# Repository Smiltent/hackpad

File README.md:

# Smil's Hackpad
a Mini-keyboard (Marcopad) provided by Hackclub's Blueprint YSWS
# Features
* mmm... funny macro buttons!
* mmm... two funny little leds that may or may not work
# Images
## PCB & Schematic
If you look at the previous commit, you can see how much I hated my v1 PCB design. I don't even want to share it...  

## CAD model
(insert image here)
# Challenges
Getting Fusion360 on Linux...  
I tried every method, trying my hardest to NOT go on Windows, but at the end, I gave up and went on Windows...
# End Result
I feel like later on, I will try and design a better case for it, as the current one is made help with the guide.  
This has actually inspired me to try and make something else down the line.  
# BOM
* 1x SEEEDUINO XIAO RP2040
* 8x Cherry MX Switches
* 2x SK6812 MINI Leds
* 4x Blank DSA Keycaps
* 4x M3x16 Bolt
* 4x M3 Heatset

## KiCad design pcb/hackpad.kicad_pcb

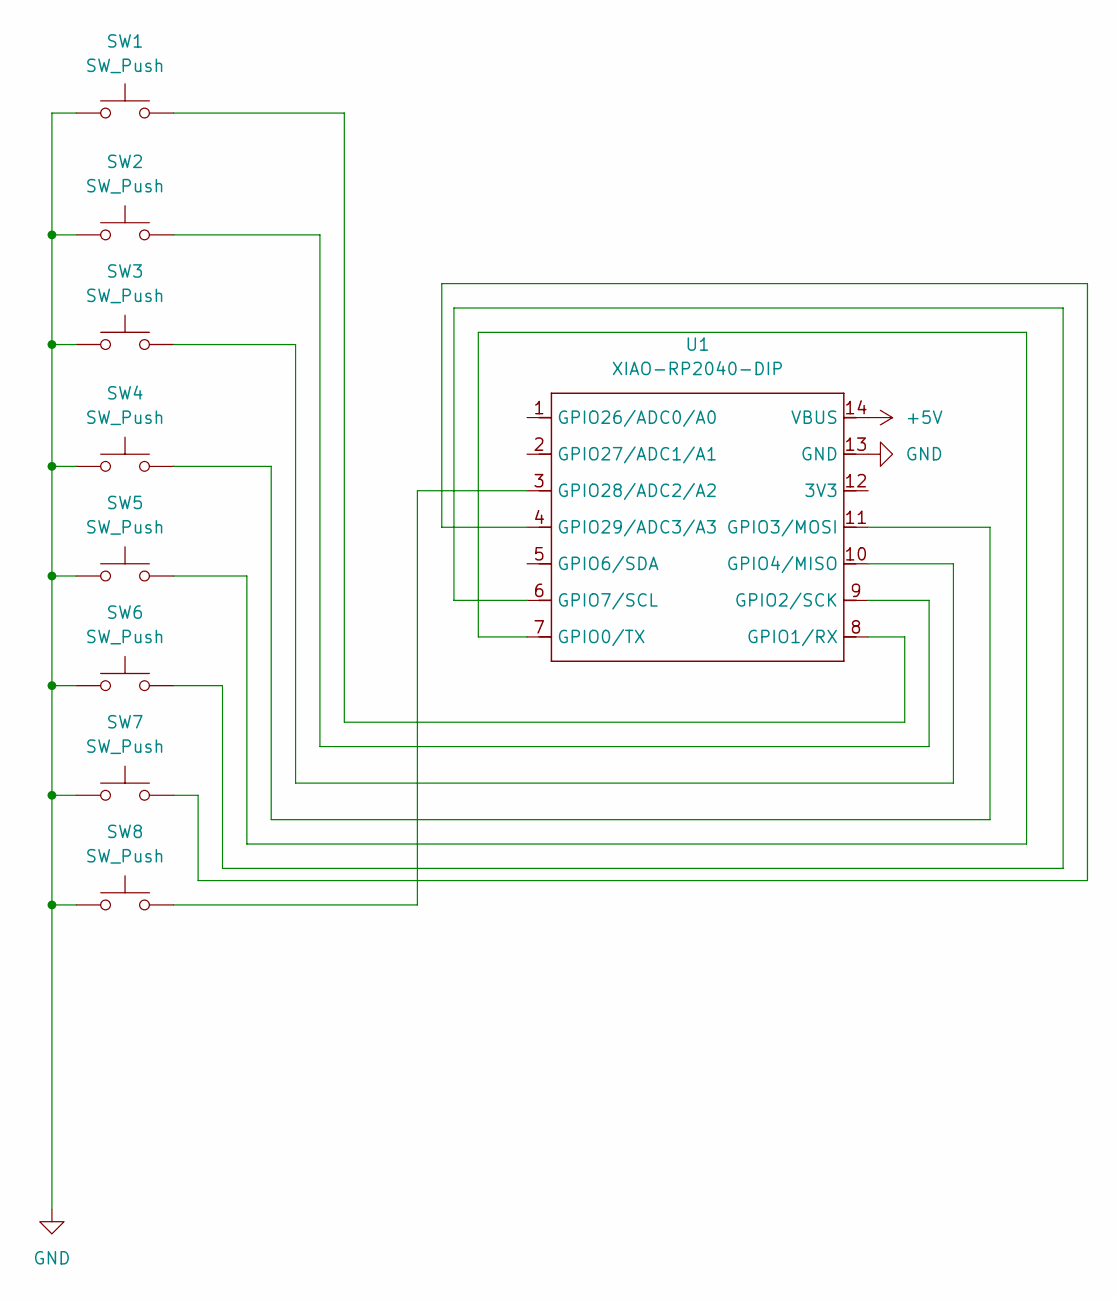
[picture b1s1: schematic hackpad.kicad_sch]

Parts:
SW1, SW2, SW3, SW4, SW5, SW6, SW7, SW8: SW_Push; SW_Cherry_MX_1.00u_PCB
U1: XIAO-RP2040-DIP

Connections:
+5V: U1.14 (VBUS)
GND: SW1.1, SW2.1, SW3.1, SW4.1, SW5.1, SW6.1, SW7.1, SW8.1, U1.13 (GND)
unnamed: SW5.2, U1.7 (GPIO0/TX)
unnamed: SW1.2, U1.8 (GPIO1/RX)
unnamed: SW2.2, U1.9 (GPIO2/SCK)
unnamed: SW4.2, U1.11 (GPIO3/MOSI)
unnamed: SW3.2, U1.10 (GPIO4/MISO)
unnamed: SW6.2, U1.6 (GPIO7/SCL)
unnamed: SW8.2, U1.3 (GPIO28/ADC2/A2)
unnamed: SW7.2, U1.4 (GPIO29/ADC3/A3)

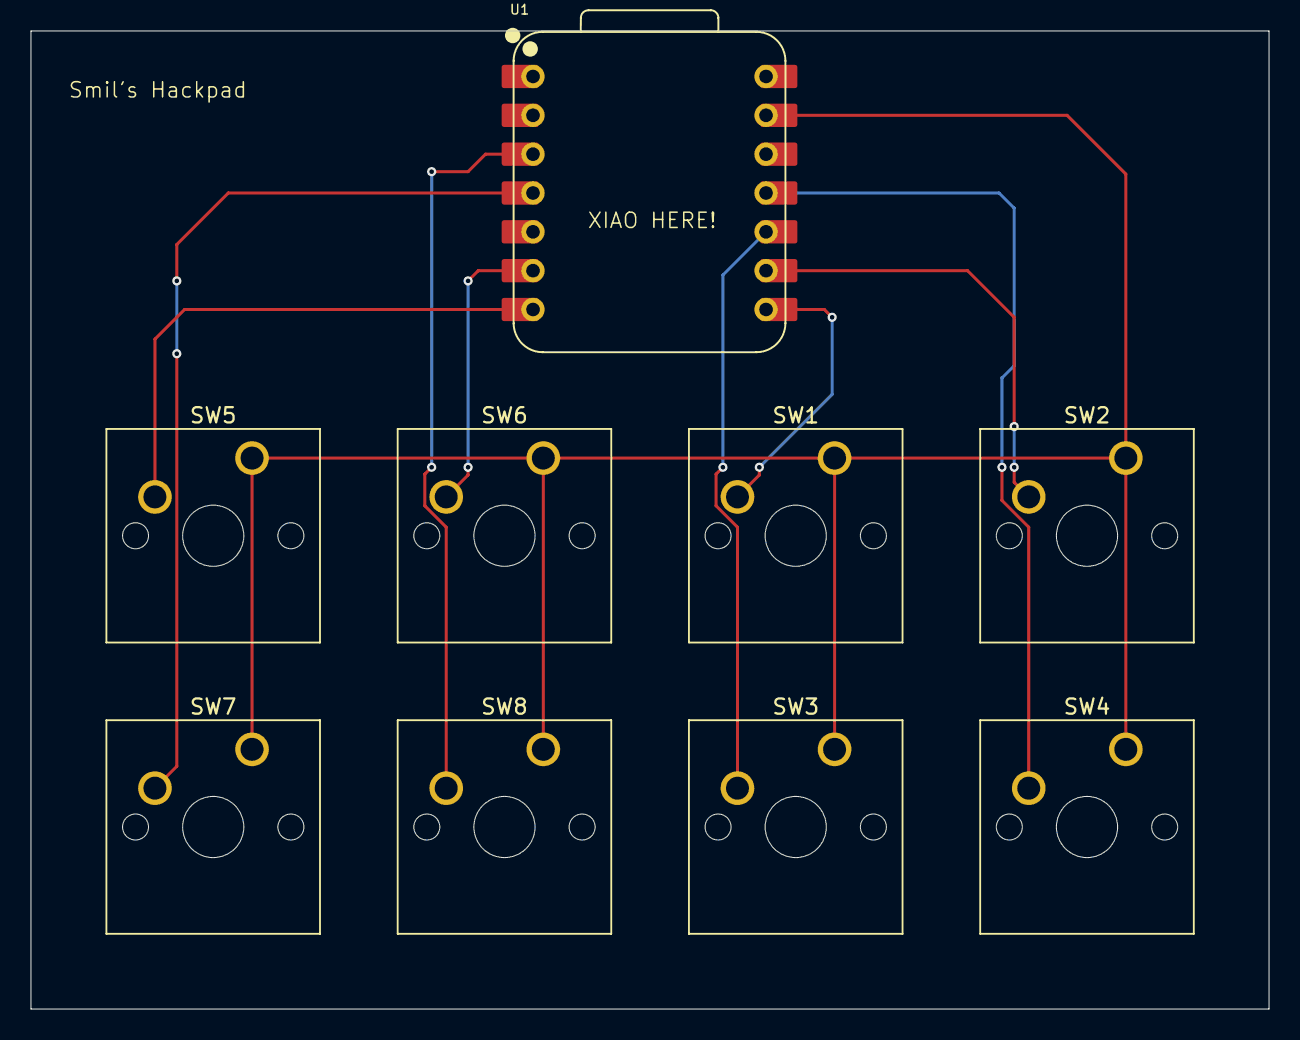
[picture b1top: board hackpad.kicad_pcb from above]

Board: 2 copper layers, 81.0 x 64.0 mm, 9 parts (0 on the bottom side), 9 nets.

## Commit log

2025-12-29 init
2025-12-29 add pcb and schem files, edit readme, add images, remove tmp
2025-12-29 fix spacing
